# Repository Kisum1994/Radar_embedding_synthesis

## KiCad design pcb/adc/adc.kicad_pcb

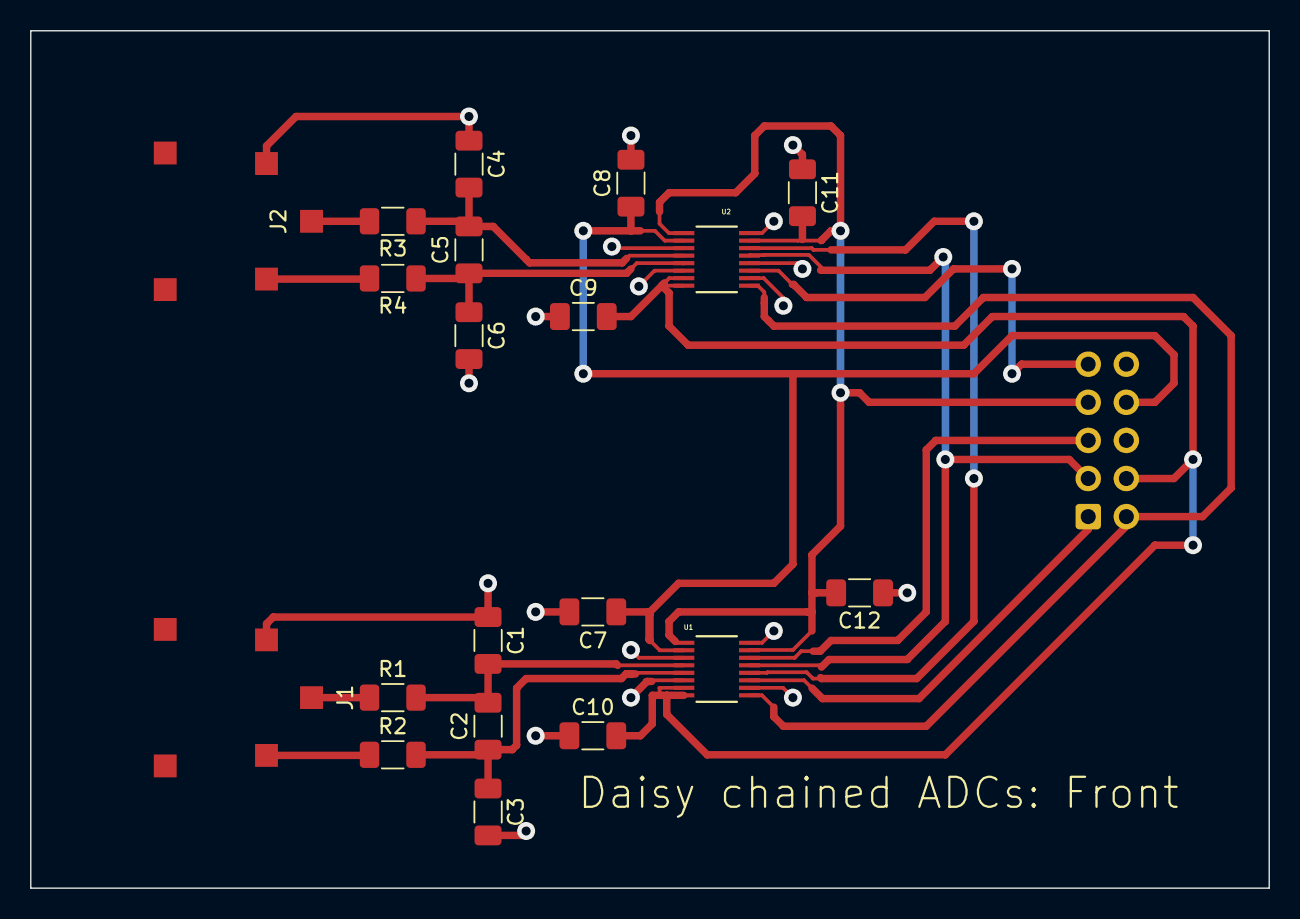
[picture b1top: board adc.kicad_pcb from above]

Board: 2 copper layers, 82.6 x 57.1 mm, 21 parts (1 on the bottom side), 18 nets.

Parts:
C1, C2, C3, C4, C5, C6: 3300pF; C_1206_3216Metric_Pad1.33x1.80mm_HandSolder
C7, C8: 100nF; C_1206_3216Metric_Pad1.33x1.80mm_HandSolder
C9, C10: 47uF; C_1206_3216Metric_Pad1.33x1.80mm_HandSolder
C11, C12: 0.1uF; C_1206_3216Metric_Pad1.33x1.80mm_HandSolder
J1, J2: AudioJack3; Lumberg_1503_03
J3: Conn_01x10_Male; IDC-Header_2x05_P2.54mm_Vertical
R1, R2, R3, R4: 20 Ohm; R_1206_3216Metric_Pad1.30x1.75mm_HandSolder
U1, U2: LTC2380CMS-16PBF; MSOP-16_MS

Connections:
GND: C1.1, C3.2, C4.1, C6.2, C7.1, C8.1, C9.2, C10.2, C11.1, C12.1, J1.S, J2.S, U1.3, U1.6, U1.10, U1.16, U2.3, U2.6, U2.10, U2.12, U2.16
unnamed: C1.2, C2.1, R1.1, U1.4
unnamed: C2.2, C3.1, R2.1, U1.5
unnamed: C4.2, C5.1, R3.1, U2.4
unnamed: C5.2, C6.1, R4.1, U2.5
unnamed: C7.2, C8.2, J3.8, U1.2, U2.2
unnamed: C9.1, C10.1, J3.4, U1.7, U1.8, U2.7, U2.8
unnamed: C11.2, C12.2, J3.7, U1.1, U1.15, U2.1, U2.15
unnamed: J1.R, R1.2
unnamed: J1.T, R2.2
unnamed: J2.R, R3.2
unnamed: J2.T, R4.2
unnamed: J3.1, U1.11
unnamed: J3.2, U1.9, U2.9
unnamed: J3.3, U1.13, U2.13
unnamed: J3.5, U1.14
unnamed: J3.9, U2.11
unnamed: U1.12, U2.14

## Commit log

2021-09-14 Add files via upload
    PCB design through KiCAD for the ADC-connection between the radar and the Pi4
